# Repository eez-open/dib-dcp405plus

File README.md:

### This is a WORK IN PROGRESS!

---

### Ownership and License
The contributors are listed in CONTRIB.TXT. 

Licenses | OSHWA UID
--|--
 | 

### Overview

The EEZ DIB DCP405+ Power module is an improved version of the [DCP405](https://github.com/eez-open/modular-psu/tree/master/dcp405) module that now includes an on-board 32-bit MCU, a more accurate and faster A/D converter for simultaneous voltage and current measurement (and thus more accurate power measurement).
This version features remote current programming in addition to the existing remote voltage programming. Sense inputs are also on 4 mm safety sockets, which now enables usage of widely available (e.g. AliExpress, eBay, etc.) and affordable Kelvin cable sets (Power/Sense) usually used with LCR meters (see below)

### Feature list
- Power input: 48 Vdc (e.g. Mean Well EPP-150-48 or LRS-150F-48)
- Max. output power: 155 W (as limited with Mean Well AC/DC module capacity) 
- Voltage regulation (CV), 0 – 40 V. Voltage set resolution (_U_SET_): 16-bit, read resolution (_U_MON_): 15-bit
- Current regulation (CC) with 2-range (50 mA, 5 A). Current set resolution (_I_SET_): 16-bit, Current read resolution (_I_MON_): 20-bit for each range
- On-board low EMI switching power pre-regulator and bias power supply
- On-board OVP with full range dual crowbar (triac/MOSFET) and 20x5 mm fuse
- Down-programmer
- Output enable (OE) circuit with LED indicator combined with coupling indication
- Ø4 mm sockets (19.05 mm/0.75” pitch) for Power outputs and Sense inputs 
- Pass-thru connector for power output coupling with other power boards for e.g. doubling output voltage (up to 80 V) or current (up to 10 A)
- Remote voltage sense with LED indicator and inverse polarity protection
- Remote voltage and current programming with LED indicator (+2.5 V for full range)
- On-board 32-bit 250 MHz MCU ([STM32H503CBT6](https://www.st.com/en/microcontrollers-microprocessors/stm32h503cb.html))
- Galvanically isolated SPI bus
- I2C EEPROM for storing board specific configuration and calibration parameters
- SPI Temperature sensor
- Dimensions: 180 x 103.5 mm, 4-layer PCB
- **CE certified design**

---

This work is financed by [NLnet](https://nlnet.nl/project/BB3-CM5/) foundation

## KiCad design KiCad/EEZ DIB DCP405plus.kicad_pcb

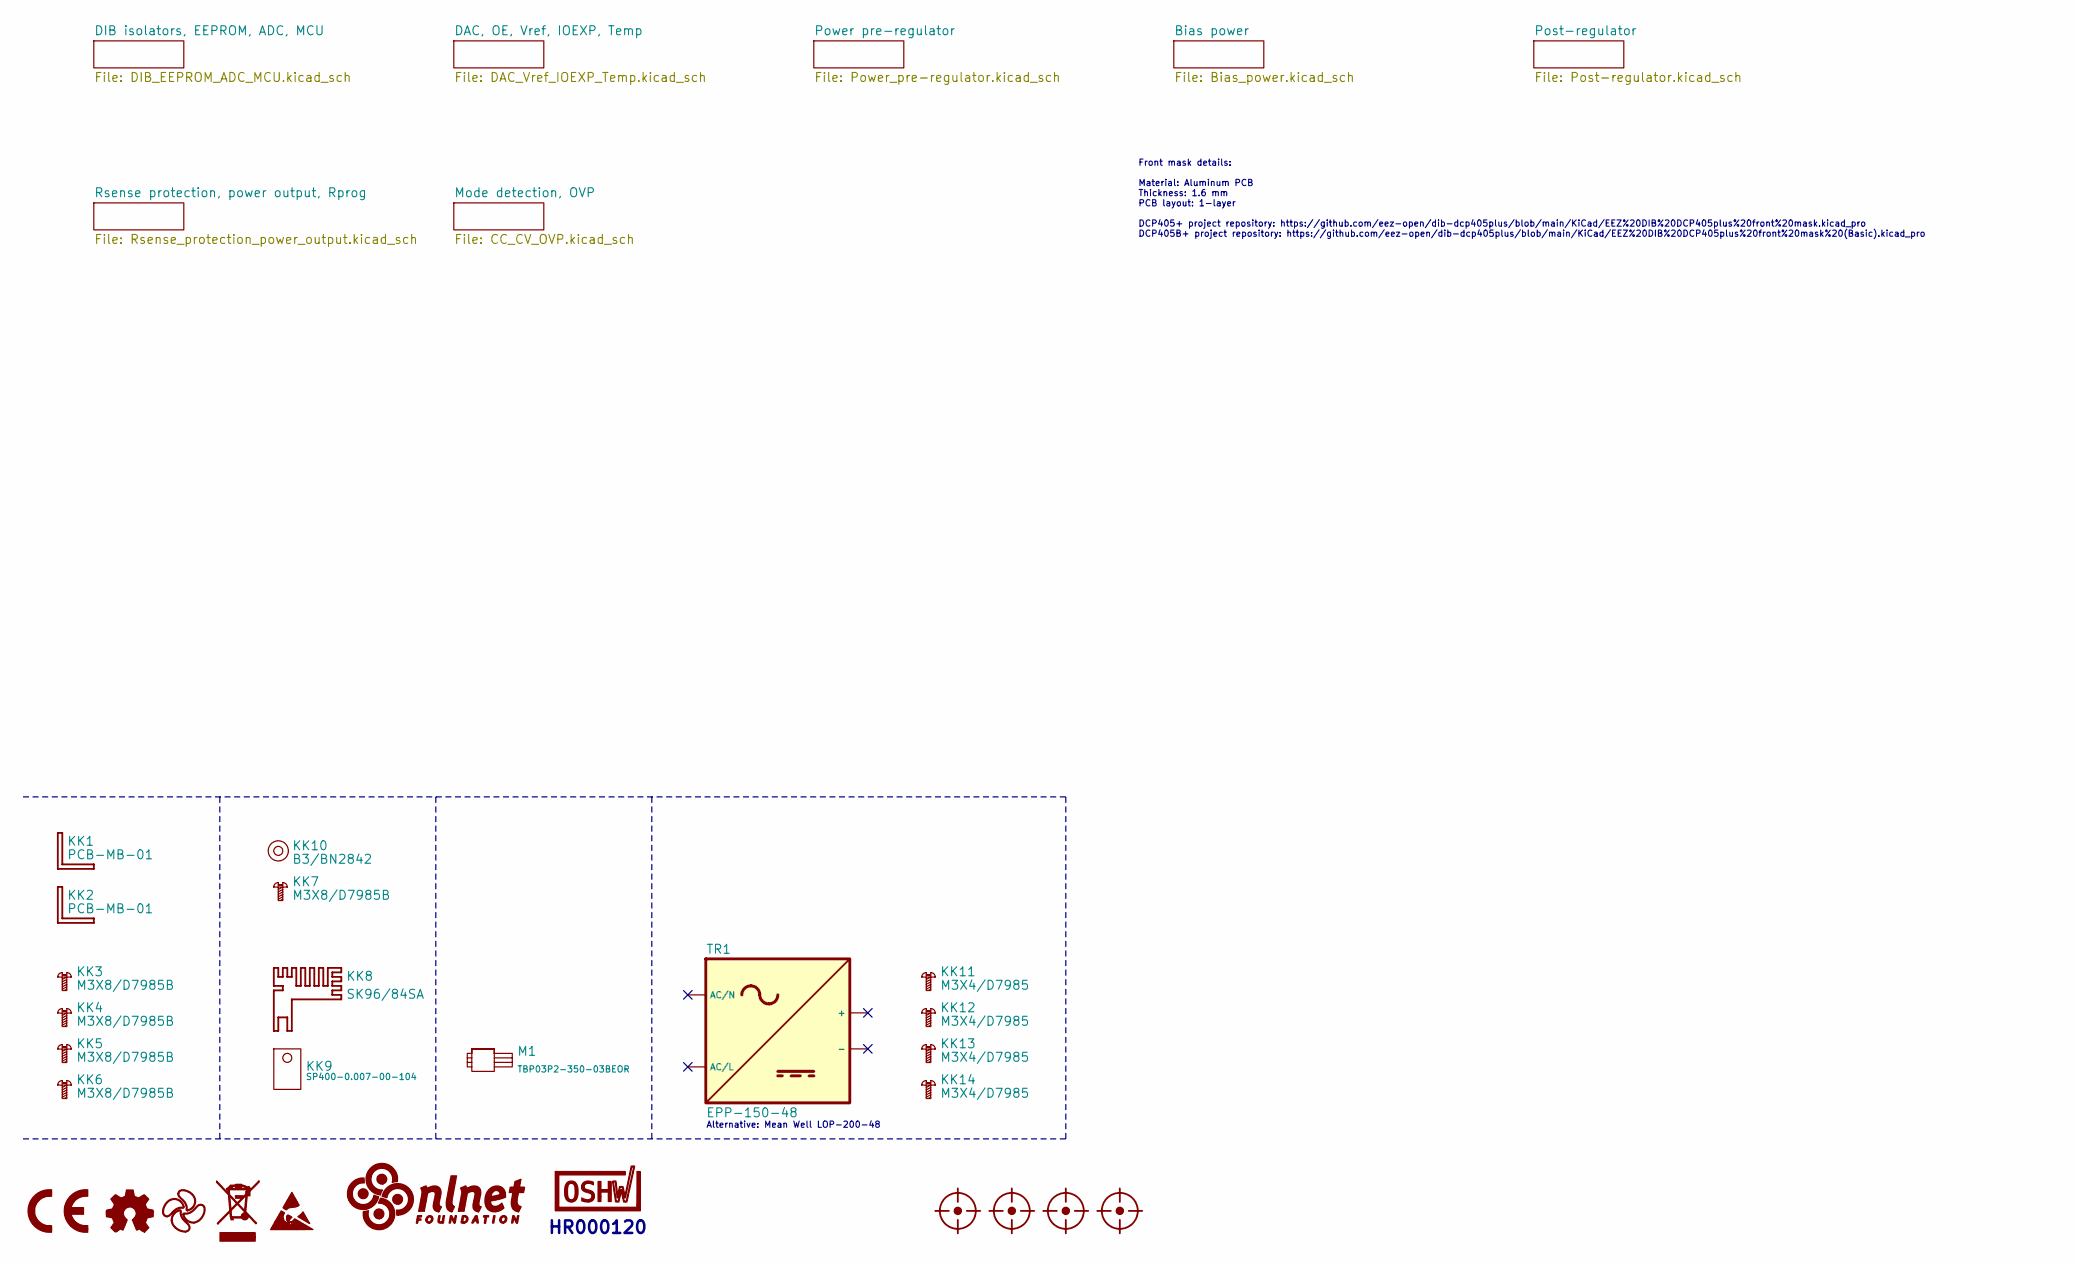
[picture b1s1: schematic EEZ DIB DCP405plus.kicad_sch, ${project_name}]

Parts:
FM1, FM2, FM3, FM4: FIDUCIAL; Fiducial_0.75mm_Mask1.5mm
KK1, KK2: PCB-MB-01; DigiKey RPC1760-ND
KK3, KK4, KK5, KK6, KK7: M3X8/D7985B
KK8: SK96/84SA; SK96_84; DigiKey 5496-SK9684SA-ND
KK9: SP400-0.007-00-104; DigiKey BER204-ND
KK10: B3/BN2842
KK11, KK12, KK13, KK14: M3X4/D7985
LOGO1: CR logo; CE logo
LOGO2: Open HW logo
LOGO3: EEZ logo; EEZ logo (outline 6mm)
LOGO4: WEEE logo
LOGO5: ESD logo
LOGO6: NLnet logo
LOGO7: OSHWA logo; OSHWA logo 6.6mm
M1: TBP03P2-350-03BEOR; DigiKey 2223-TBP03P2-350-03BEOR-ND
TR1: EPP-150-48; DigiKey 1866-LOP-200-48-ND

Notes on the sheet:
Alternative: Mean Well LOP-200-48
HR000120
Front mask details: Material: Aluminum PCB Thickness: 1.6 mm PCB layout: 1-layer DCP405+ project repository: https://github.com/eez-open/dib-dcp405plus/blob/main/KiCad/EEZ%20DIB%20DCP405plus%20front%20mask.kicad_pro DCP405B+ project repository: https://github.com/eez-open/dib-dcp405plus/blob/main/K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

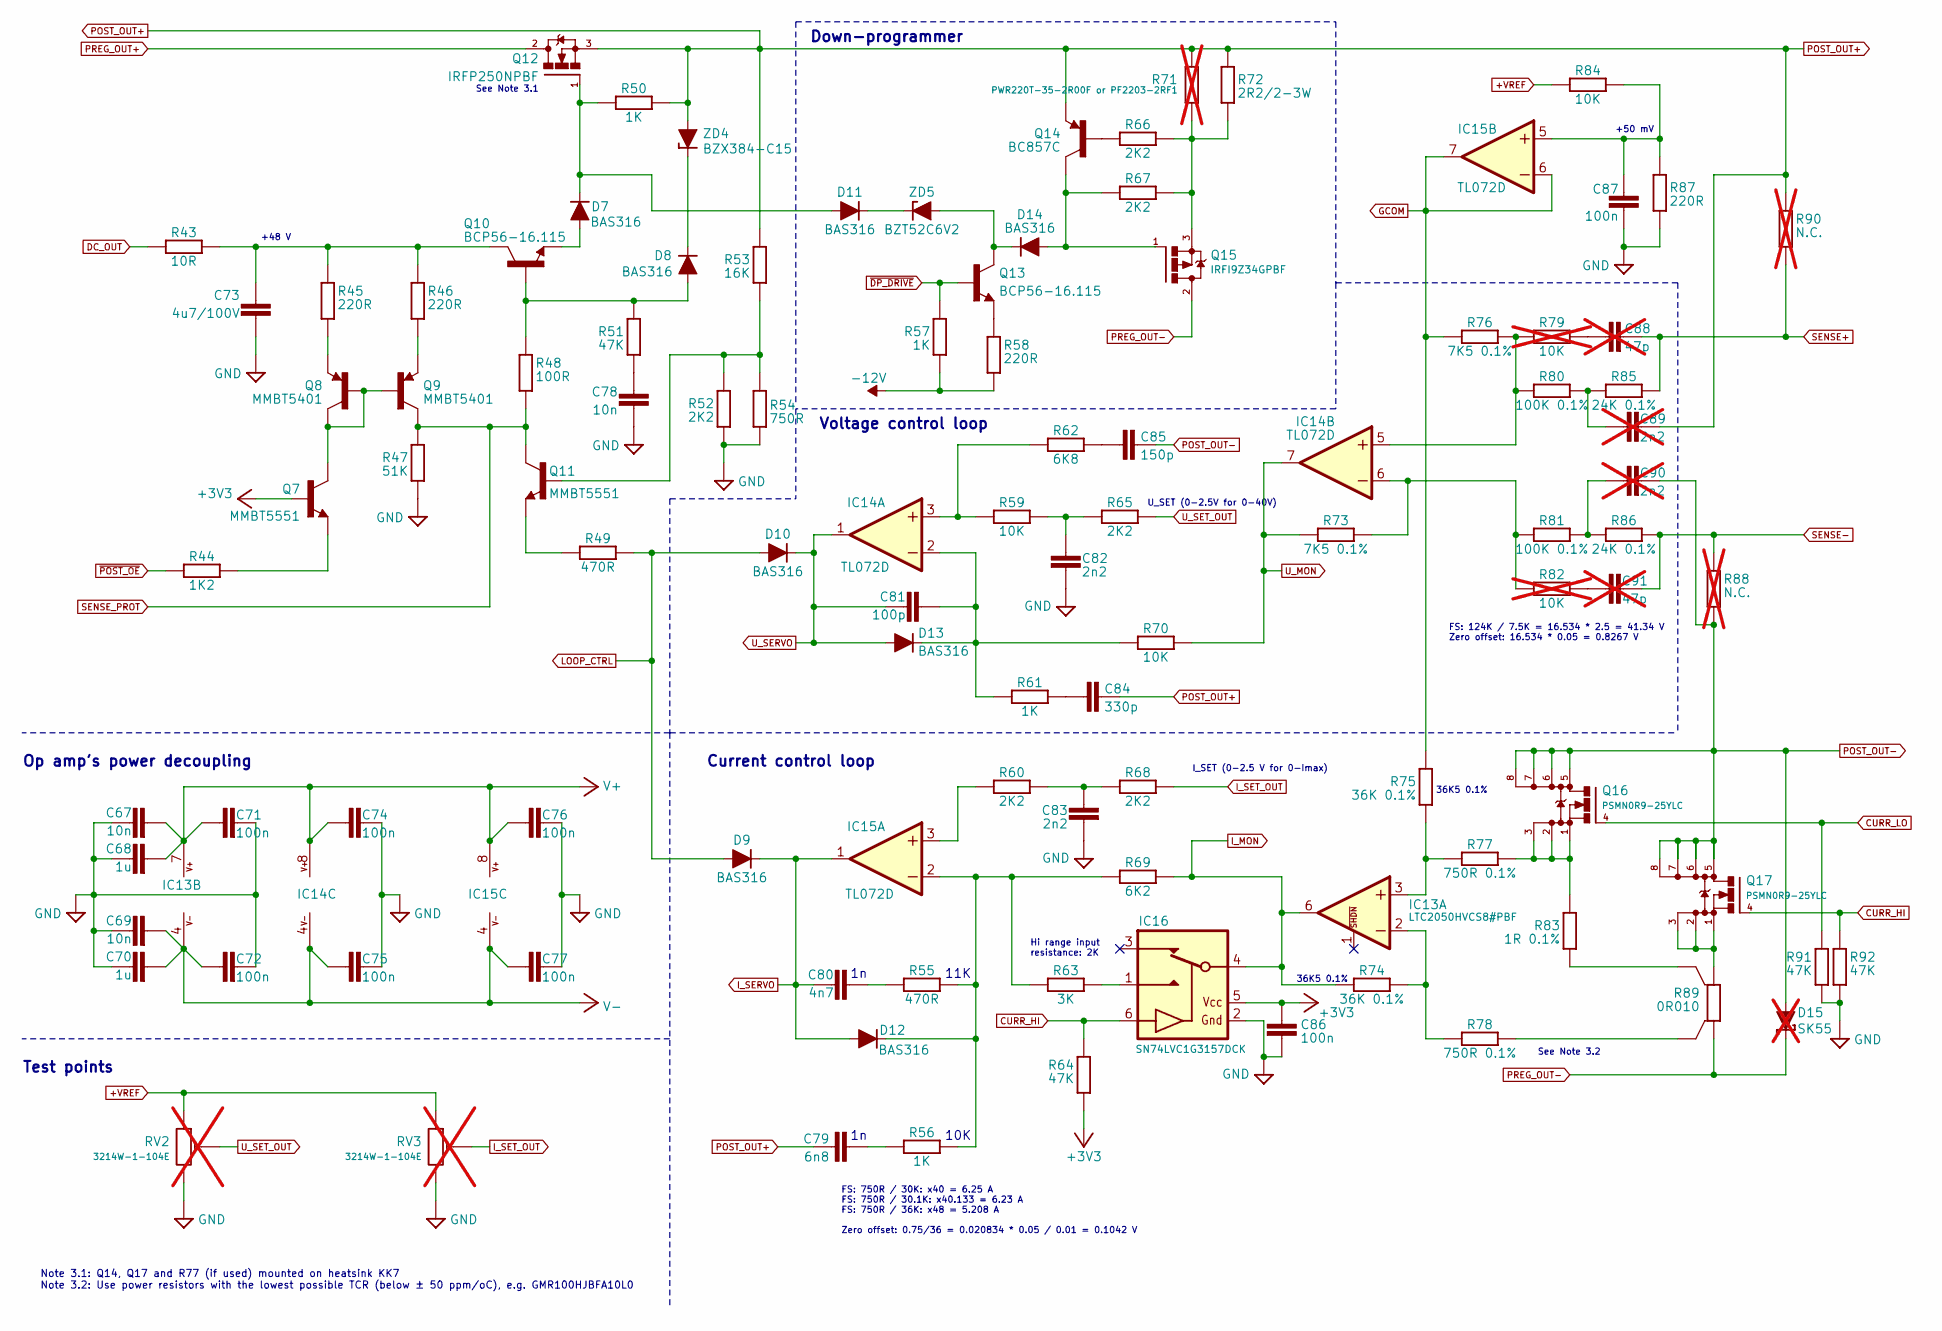
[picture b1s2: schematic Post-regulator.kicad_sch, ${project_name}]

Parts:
C67, C69, C78: 10n; C_0805_2012Metric; DigiKey 490-7194-1-ND
C68, C70: 1u; C_0805_2012Metric; DigiKey 1276-2931-1-ND
C71, C72, C74, C75, C76, C77, C86, C87: 100n; C_0603_1608Metric; DigiKey 1276-6717-1-ND
C73: 4u7/100V; C_1210_3225Metric; DigiKey 587-5034-1-ND
C79: 6n8; C_0805_2012Metric; DigiKey 399-C0805C682K5RACTUCT-ND
C80: 4n7; C_0805_2012Metric; DigiKey 732-12255-1-ND
C81: 100p; C_0805_2012Metric; DigiKey 399-15000-1-ND
C82, C83: 2n2; C_0805_2012Metric; DigiKey 1276-2478-1-ND
C84: 330p; C_0805_2012Metric; DigiKey 311-1117-1-ND
C85: 150p; C_0805_2012Metric; DigiKey 732-7853-1-ND
C88, C91: 47p; C_0805_2012Metric; not fitted
C89, C90: 2n2; C_0805_2012Metric; DigiKey 399-C0805C222K5RAC7210TR-ND; not fitted
D7, D8, D9, D10, D11, D12, D13, D14: BAS316; SOD-323_1P8X1P35_ONS-M; DigiKey 5399-BAS316CT-ND
D15: SK55; DO214AA; DigiKey SK56A-LTPMSCT-ND; not fitted
IC13: LTC2050HVCS8#PBF; SOIC127P600X173-8N; DigiKey LTC2050HVCS8#TRPBFCT-ND
IC14, IC15: TL072D; SOIC127P600X173-8N; DigiKey 296-1282-1-ND
IC16: SN74LVC1G3157DCK; SOT65P210X110-6N; DigiKey 296-14909-1-ND
Q7, Q11: MMBT5551; SOT23-BEC; DigiKey MMBT5551LT1GOSCT-ND
Q8, Q9: MMBT5401; SOT23-BEC; DigiKey MMBT5401-FDICT-ND
Q10, Q13: BCP56-16.115; SOT223-BCE; DigiKey 5399-BCP56-16CT-ND
Q12: IRFP250NPBF; TO247-3_SUNKEN; DigiKey IRFP250PBF-ND
Q14: BC857C; SOT23-BEC; DigiKey 4878-BC857CCT-ND
Q15: IRFI9Z34GPBF; TO220FP-V; DigiKey IRFI9Z34GPBF-ND
Q16, Q17: PSMN0R9-25YLC; TDSON-8; DigiKey 1727-5292-1-ND
R43: 10R; R_0805_2012Metric; DigiKey 311-10.0CRCT-ND
R44: 1K2; R_0805_2012Metric; DigiKey 311-1.20KCRCT-ND
R45, R46, R58, R87: 220R; R_0805_2012Metric; DigiKey RMCF0805FT220RCT-ND
R47: 51K; R_0805_2012Metric; DigiKey 311-51.0KCRCT-ND
R48: 100R; R_0603_1608Metric; DigiKey 13-RC0603FR-10100RLCT-ND
R49, R55: 470R; R_0805_2012Metric; DigiKey 13-RC0805FR-13470RLCT-ND
R50, R56, R57, R61: 1K; R_0805_2012Metric; DigiKey 311-1.00KCRCT-ND
R51, R64, R91, R92: 47K; R_0805_2012Metric; DigiKey RHM47KKCT-ND
R52, R60, R65, R66, R67, R68: 2K2; R_0805_2012Metric; DigiKey 311-2.20KCRCT-ND
R53: 16K; R_0805_2012Metric; DigiKey 311-16.0KCRCT-ND
R54: 750R; R_0805_2012Metric; DigiKey A126385CT-ND
R59, R70, R84: 10K; R_0805_2012Metric; DigiKey 311-10.0KCRCT-ND
R62: 6K8; R_0805_2012Metric; DigiKey 311-6.80KCRCT-ND
R63: 3K; R_0603_1608Metric; DigiKey 311-3.00KCRCT-ND
R69: 6K2; R_0805_2012Metric; DigiKey 311-6.20KCRCT-ND
R71: PWR220T-35-2R00F or PF2203-2RF1; TO220-2-V; DigiKey 696-1313-ND; not fitted
R72: 2R2/2-3W; R_2512_6332Metric; DigiKey CRM2512-JW-2R2ELFCT-ND
R73, R76: 7K5 0.1%; R_0805_2012Metric; DigiKey YAG1974CT-ND
R74, R75: 36K 0.1%; R_0805_2012Metric; DigiKey YAG4886CT-ND
R77, R78: 750R 0.1%; R_0805_2012Metric; DigiKey YAG4940CT-ND
R79, R82: 10K; R_0805_2012Metric; not fitted
R80, R81: 100K 0.1%; R_0805_2012Metric; DigiKey YAG4808CT-ND
R83: 1R 0.1%; R_1206_3216Metric; DigiKey 1712-CPF1206B1R0E1CT-ND
R85, R86: 24K 0.1%; R_0805_2012Metric; DigiKey P24KBFCT-ND
R88, R90: N.C.; R_0805_2012Metric; not fitted
R89: 0R010; R_2512-4WIRE; DigiKey 846-GMR100HJBFA10L0CT-ND
RV2, RV3: 3214W-1-104E; TRIM_3214W-1-104E; DigiKey 3214W-104ECT-ND; not fitted
ZD4: BZX384-C15; SOD-323_1P8X1P35_ONS-M; DigiKey 1727-BZX384-C15-QFCT-ND
ZD5: BZT52C6V2; SOD123; DigiKey 4878-BZT52C6V2CT-ND

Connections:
+3V3: C86.1, IC16.5 (VDD), Q7.B, R64.1; also elsewhere on the board
+VREF: R84.1, RV2.1, RV3.1; also elsewhere on the board
-12V: R57.2, R58.2; also elsewhere on the board
CURR_HI: IC16.6 (CTRL), Q17.4 (G), R64.2, R92.2; also elsewhere on the board
CURR_LO: Q16.4 (G), R91.2; also elsewhere on the board
DC_OUT: R43.2; also elsewhere on the board
GCOM: IC15.6 (-IN), IC15.7 (OUT), R75.1, R76.1; also elsewhere on the board
GND: C67.1, C68.1, C69.1, C70.1, C71.2, C72.2, C73.2, C74.1, C75.1, C76.1, C77.1, C78.2, C82.2, C83.2, C86.2, C87.2, IC16.2 (GND), R47.1, R52.1, R54.1, R87.2, R91.1, R92.1, RV2.3, RV3.3; also elsewhere on the board
I_MON: IC13.6 (OUT), IC16.4 (COM), R69.1, R74.2; also elsewhere on the board
I_SERVO: C80.2, D9.C, D12.A, IC15.1 (OUT); also elsewhere on the board
I_SET_OUT: R68.1, RV3.2; also elsewhere on the board
LOOP_CTRL: D9.A, D10.A, R49.1; also elsewhere on the board
unnamed: C73.1, Q10.C, R43.1, R45.2, R46.2
unnamed: C78.1, R51.1
unnamed: C79.2, R56.1
unnamed: C80.1, R55.1
unnamed: C82.1, R59.1, R65.2
unnamed: C83.1, R60.1, R68.2
unnamed: C84.2, R61.1
unnamed: C85.2, R62.1
unnamed: C88.2, R79.1
unnamed: C89.1, R80.2, R85.1
unnamed: C90.1, R81.2, R86.1
unnamed: C91.2, R82.1
unnamed: D7.A, Q10.E
unnamed: D8.A, Q10.B, R48.1, R51.2
unnamed: D8.C, ZD4.C
unnamed: D11.C, ZD5.C
unnamed: D14.C, Q13.C, ZD5.A
unnamed: IC13.3 (+IN), R75.2, R77.2
unnamed: IC13.2 (-IN), R74.1, R78.2
unnamed: IC14.3 (+IN), R59.2, R62.2
unnamed: C81.1, D13.C, IC14.2 (-IN), R61.2, R70.2
unnamed: IC14.5 (+IN), R76.2, R79.2, R80.1
unnamed: IC14.6 (-IN), R73.2, R81.1, R82.2
unnamed: IC15.3 (+IN), R60.2
unnamed: D12.C, IC15.2 (-IN), R55.2, R56.2, R63.2, R69.2
unnamed: C87.1, IC15.5 (+IN), R84.2, R87.1
unnamed: IC16.1 (NO), R63.1
unnamed: Q7.C, Q8.B, Q8.C, Q9.B
unnamed: Q7.E, R44.2
unnamed: Q8.E, R45.1
unnamed: Q9.E, R46.1
unnamed: Q11.B, R52.2, R53.1, R54.2
unnamed: Q11.E, R49.2
unnamed: D7.C, D11.A, Q12.1 (G), R50.1
unnamed: Q13.E, R58.1
unnamed: Q14.B, R66.2
unnamed: D14.A, Q14.C, Q15.1 (G), R67.2
unnamed: Q15.3 (S), R66.1, R67.1, R71.1, R72.2
unnamed: Q16.1 (S), Q16.2 (S), Q16.3 (S), R77.1, R83.2
unnamed: Q17.1 (S), Q17.2 (S), Q17.3 (S), R89.2
unnamed: R78.1, R89.1S
unnamed: R83.1, R89.2S
POST_OUT+: C79.1, C84.1, C89.2, Q12.3 (S), Q14.E, R50.2, R53.2, R71.2, R72.1, R90.1, ZD4.A; also elsewhere on the board
POST_OUT-: C85.1, C90.2, D15.A, Q16.5 (D), Q16.6 (S), Q16.7 (S), Q16.8 (S), Q17.5 (D), Q17.6 (S), Q17.7 (S), Q17.8 (S), R88.2; also elsewhere on the board
PREG_OUT+: Q12.2 (D); also elsewhere on the board
PREG_OUT-: D15.C, Q15.2 (D), R89.1; also elsewhere on the board
SENSE+: C88.1, R85.2, R90.2; also elsewhere on the board
SENSE-: C91.1, R86.2, R88.1; also elsewhere on the board
SENSE_PROT: Q9.C, Q11.C, R47.2, R48.2; also elsewhere on the board
U_MON: IC14.7 (OUT), R70.1, R73.1; also elsewhere on the board
U_SERVO: C81.2, D10.C, D13.A, IC14.1 (OUT); also elsewhere on the board
U_SET_OUT: R65.1, RV2.2; also elsewhere on the board
V+: C67.2, C68.2, C71.1, C74.2, C76.2, IC13.7 (V+), IC14.8 (V+), IC15.8 (V+); also elsewhere on the board
V-: C69.2, C70.2, C72.1, C75.2, C77.2, IC13.4 (V-), IC14.4 (V-), IC15.4 (V-); also elsewhere on the board
~DP_DRIVE: Q13.B, R57.1; also elsewhere on the board
~POST_OE: R44.1; also elsewhere on the board

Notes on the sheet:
Hi range input resistance: 2K
FS: 124K / 7.5K = 16.534 * 2.5 = 41.34 V Zero offset: 16.534 * 0.05 = 0.8267 V
11K
Down-programmer
+50 mV
I_SET (0-2.5 V for 0-Imax)
Op amp's power decoupling
See Note 3.1
36K5 0.1%
10K
Current control loop
Voltage control loop
See Note 3.2
+48 V
U_SET (0-2.5V for 0-40V)
Test points
FS: 750R / 30K: x40 = 6.25 A FS: 750R / 30.1K: x40.133 = 6.23 A FS: 750R / 36K: x48 = 5.208 A Zero offset: 0.75/36 = 0.020834 * 0.05 / 0.01 = 0.1042 V
Note 3.1: Q14, Q17 and R77 (if used) mounted on heatsink KK7 Note 3.2: Use power resistors with the lowest possible TCR (below ± 50 ppm/oC), e.g. GMR100HJBFA10L0

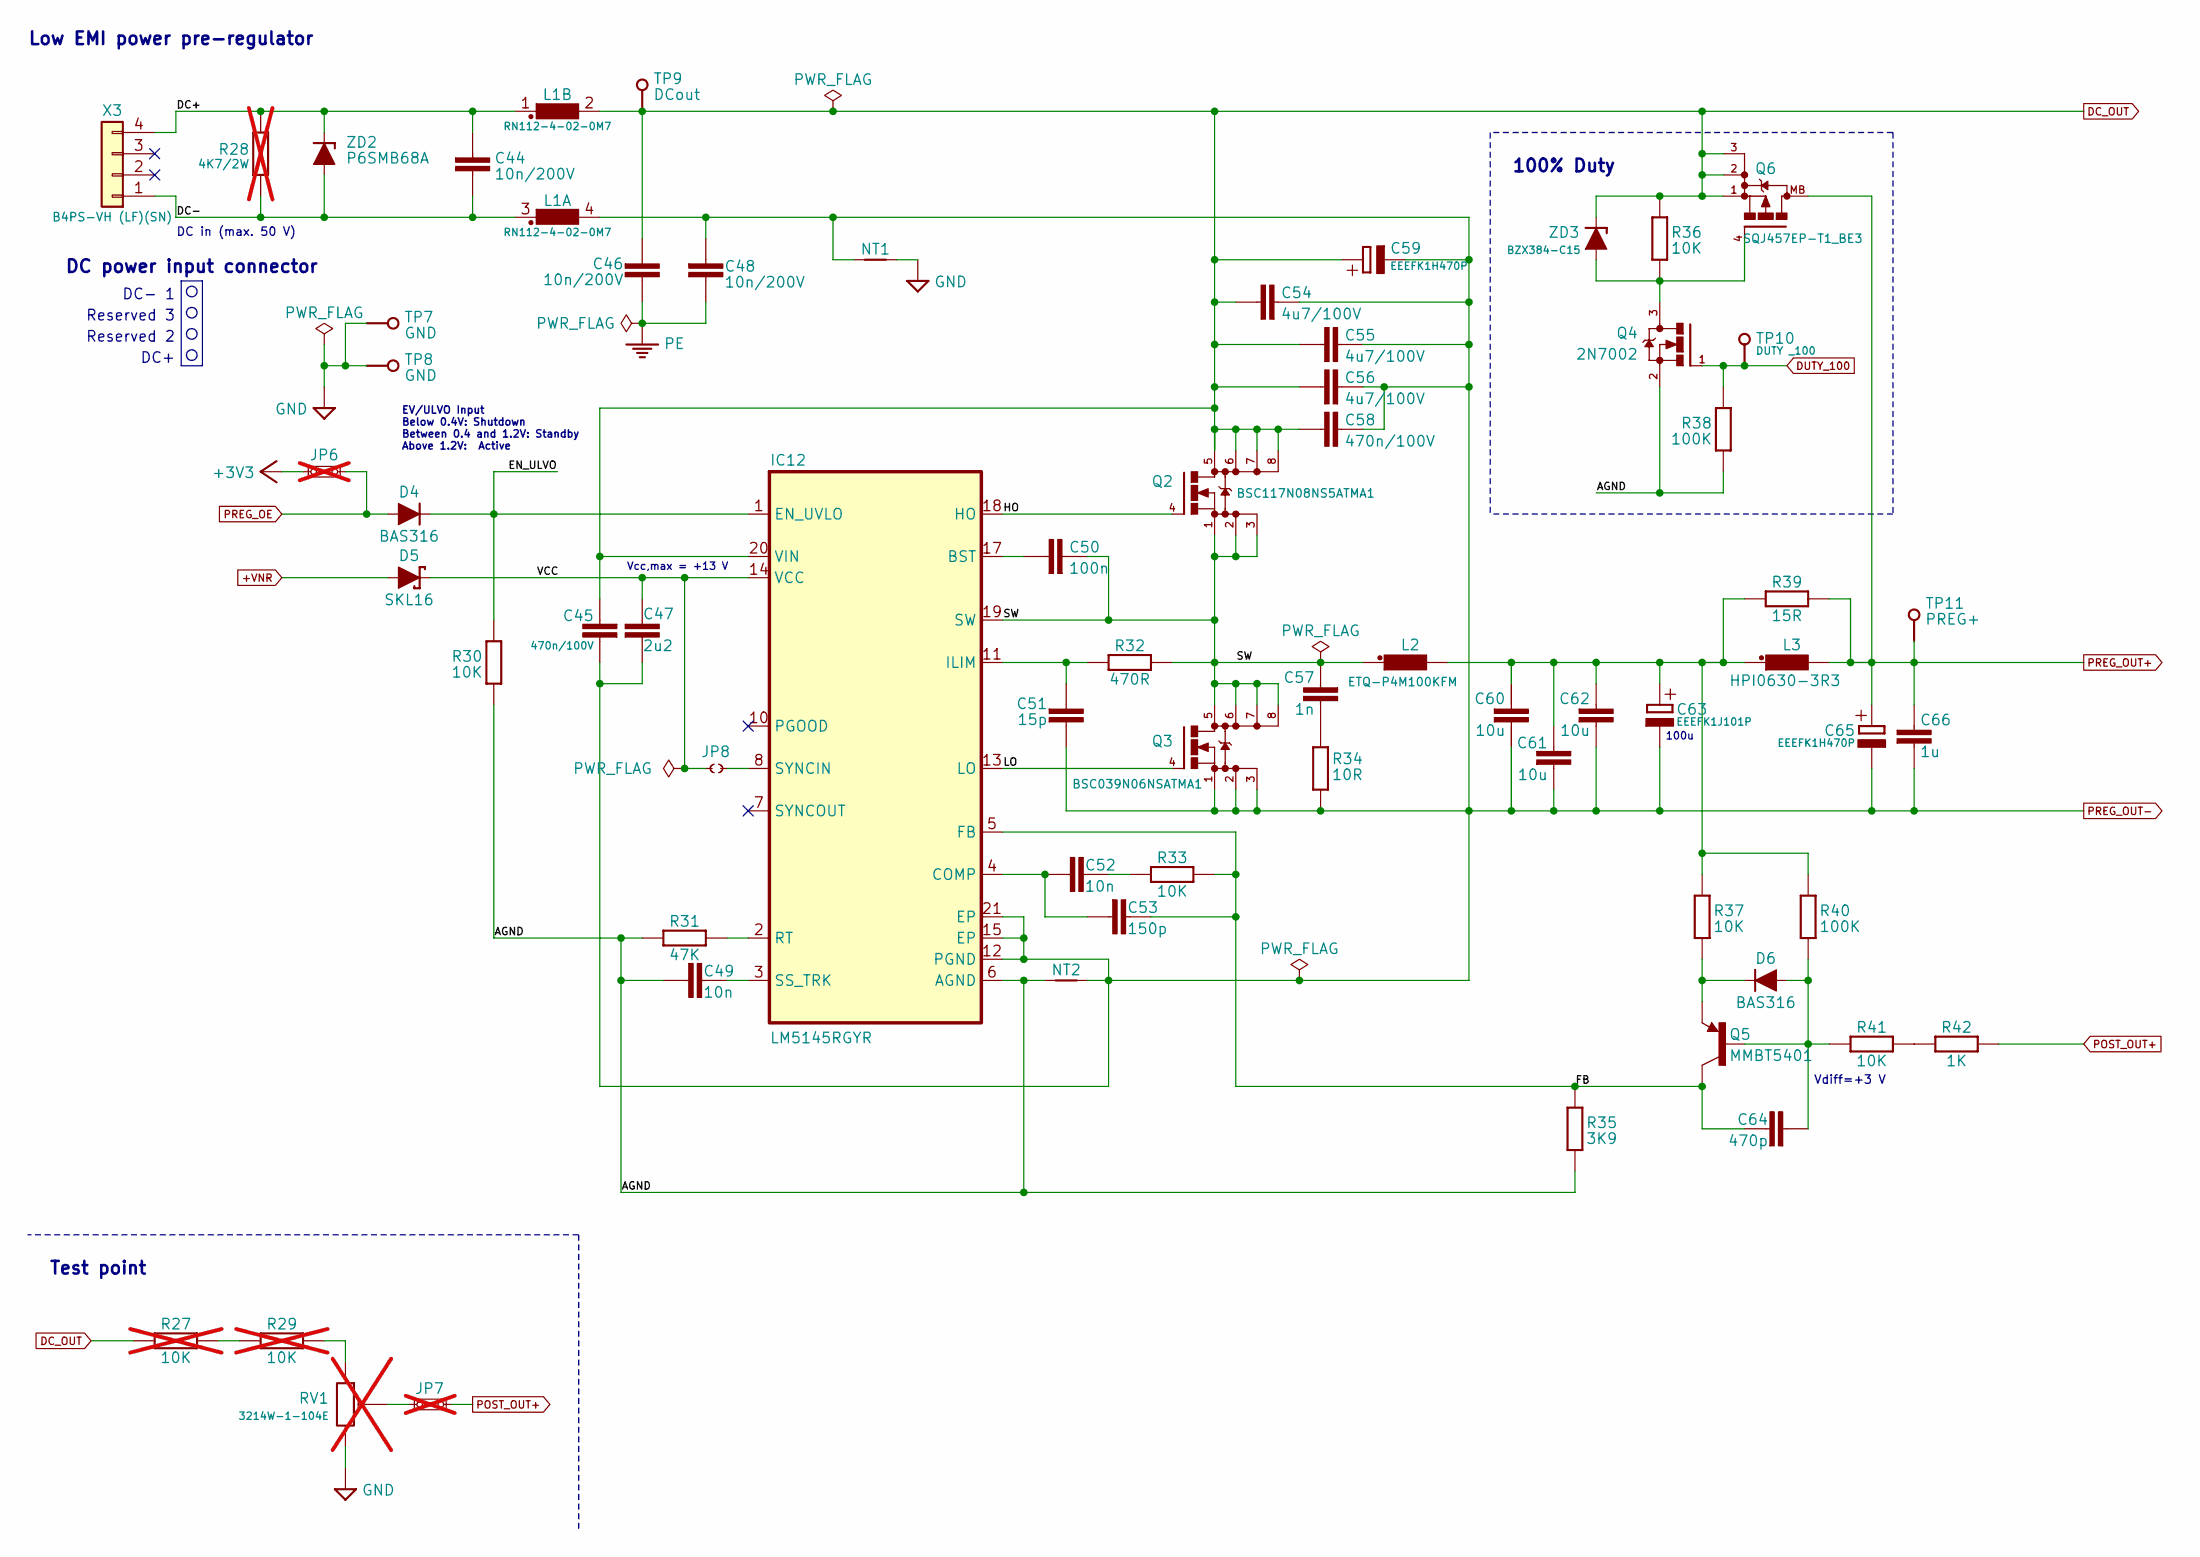
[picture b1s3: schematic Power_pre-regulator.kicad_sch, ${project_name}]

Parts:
C44, C46, C48: 10n/200V; C_1206_3216Metric; DigiKey 311-4491-1-ND
C45, C58: 470n/100V; C_0805_2012Metric; DigiKey 587-5014-1-ND
C47: 2u2; C_1206_3216Metric; DigiKey 1276-3138-1-ND
C49, C52: 10n; C_0805_2012Metric; DigiKey 490-7194-1-ND
C50: 100n; C_0603_1608Metric; DigiKey 1276-6717-1-ND
C51: 15p; C_0603_1608Metric; DigiKey 732-7847-1-ND
C53: 150p; C_0805_2012Metric; DigiKey 732-7853-1-ND
C54, C55, C56: 4u7/100V; C_1210_3225Metric; DigiKey 587-5034-1-ND
C57: 1n; C_0603_1608Metric; DigiKey 1276-1018-1-ND
C59, C65: EEEFK1H470P; CAPAE830X1050N; DigiKey PCE3815CT-ND
C60, C61, C62: 10u; C_1210_3225Metric; DigiKey 1276-3387-1-ND
C63: EEEFK1J101P; CAPAE1030X1050N; DigiKey PCE3819CT-ND
C64: 470p; C_0805_2012Metric; DigiKey 732-7837-1-ND
C66: 1u; C_0805_2012Metric; DigiKey 1276-2931-1-ND
D4, D6: BAS316; SOD-323_1P8X1P35_ONS-M; DigiKey 5399-BAS316CT-ND
D5: SKL16; SOD123; DigiKey RB160MM-60CT-ND
IC12: LM5145RGYR; RGY0020B; DigiKey 296-47121-1-ND
JP6, JP7: M22-2010246; DigiKey M22-2010346-ND; not fitted
JP8: JP2-CUT-0805; JP2 open (0603)
L1: RN112-4-02-0M7; RN112; DigiKey 817-2100-ND
L2: ETQ-P4M100KFM; PANASONIC_ETQ-P4_KFM; DigiKey P124167CT-ND
L3: HPI0630-3R3; COILCRAFT_HPI0630; DigiKey 445-180834-1-ND
NT1: NetTie_2; NetTie-2_SMD_Pad1.5mm
NT2: NetTie_2; NetTie-2_SMD_Pad0.2mm
Q2: BSC117N08NS5ATMA1; TDSON-8; DigiKey BSC117N08NS5ATMA1CT-ND
Q3: BSC039N06NSATMA1; TDSON-8; DigiKey BSC039N06NSATMA1CT-ND
Q4: 2N7002; SOT103P240X110-3N; DigiKey T2N7002AKLMCT-ND
Q5: MMBT5401; SOT23-BEC; DigiKey MMBT5401-FDICT-ND
Q6: SQJ457EP-T1_BE3; PowerPAK SO-8; DigiKey 742-SQJ457EP-T1_BE3CT-ND
R27, R29: 10K; R_0805_2012Metric; DigiKey 311-10.0KCRCT-ND; not fitted
R28: 4K7/2W; R_2512_6332Metric; not fitted
R30, R33, R36, R37, R41: 10K; R_0805_2012Metric; DigiKey 311-10.0KCRCT-ND
R31: 47K; R_0805_2012Metric; DigiKey RHM47KKCT-ND
R32: 470R; R_0805_2012Metric; DigiKey 13-RC0805FR-13470RLCT-ND
R34: 10R; R_0805_2012Metric; DigiKey 311-10.0CRCT-ND
R35: 3K9; R_0805_2012Metric; DigiKey A126369CT-ND
R38, R40: 100K; R_0805_2012Metric; DigiKey RMCF0805FT100KCT-ND
R39: 15R; R_2010_5025Metric; DigiKey A129910CT-ND
R42: 1K; R_0805_2012Metric; DigiKey 311-1.00KCRCT-ND
RV1: 3214W-1-104E; TRIM_3214W-1-104E; DigiKey 3214W-104ECT-ND; not fitted
TP7, TP8: PCB_TEST_TABSHIELD; Testhole 24_50mils
TP9, TP10, TP11: TEST-PIN_0.9MM; Testhole 24_50mils
X3: B4PS-VH (LF)(SN); B4PS-VH; DigiKey 455-B4PS-VH-ND
ZD2: P6SMB68A; DO214AA; DigiKey P6SMB68ABBCT-ND
ZD3: BZX384-C15; SOD-323_1P8X1P35_ONS-M; DigiKey 1727-4986-1-ND

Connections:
+3V3: JP6.1; also elsewhere on the board
+VNR: D5.A; also elsewhere on the board
/Power pre-regulator/AGND: C49.2, IC12.6 (AGND), NT2.1, Q4.2 (S), R30.1, R31.1, R35.2, R38.2
/Power pre-regulator/DC+: C44.2, L1.1, R28.1, X3.4, ZD2.C
/Power pre-regulator/DC-: C44.1, L1.3 (1), R28.2, X3.1, ZD2.A
/Power pre-regulator/EN_ULVO: D4.C, IC12.1 (EN_UVLO), R30.2
/Power pre-regulator/FB: C53.1, C64.1, IC12.5 (FB), Q5.C, R33.2, R35.1
/Power pre-regulator/HO: IC12.18 (HO), Q2.4 (G)
/Power pre-regulator/LO: IC12.13 (LO), Q3.4 (G)
/Power pre-regulator/SW: C50.2, C57.1, IC12.19 (SW), L2.1, Q2.1 (S), Q2.2 (S), Q2.3 (S), Q3.5 (D), Q3.6 (S), Q3.7 (S), Q3.8 (S), R32.2
/Power pre-regulator/VCC: C47.2, D5.C, IC12.14 (VCC), JP8.1
DC_OUT: C45.2, C46.2, C54.1, C55.1, C56.1, C58.2, C59.+, IC12.20 (VIN), L1.2, Q2.5 (D), Q2.6 (S), Q2.7 (S), Q2.8 (S), Q6.1 (S), Q6.2 (S), Q6.3 (S), R27.2, R36.2, TP9.1 (P$1_1), ZD3.C; also elsewhere on the board
DUTY_100: Q4.1 (G), R38.1, TP10.1 (P$1_1); also elsewhere on the board
GND: NT1.2, RV1.3, TP7.1 (P$1_1), TP8.1 (P$1_1); also elsewhere on the board
unnamed: C52.1, R33.1
unnamed: C57.2, R34.2
unnamed: C60.1, C61.1, C62.1, C63.+, L2.2, L3.1, R37.1, R39.2, R40.1
unnamed: C64.2, D6.A, Q5.B, R40.2, R41.1
unnamed: D6.C, Q5.E, R37.2
unnamed: C50.1, IC12.17 (BST)
unnamed: C52.2, C53.2, IC12.4 (COMP)
unnamed: C51.1, IC12.11 (ILIM), R32.1
unnamed: IC12.2 (RT), R31.2
unnamed: C49.1, IC12.3 (SS_TRK)
unnamed: IC12.8 (SYNCIN), JP8.2
unnamed: JP7.1, RV1.2
unnamed: Q4.3 (D), Q6.4 (G), R36.1, ZD3.A
unnamed: R27.1, R29.2
unnamed: R29.1, RV1.1
unnamed: R41.2, R42.1
PE: C46.1, C48.2; also elsewhere on the board
POST_OUT+: JP7.2, R42.2; also elsewhere on the board
PREG_OE: D4.A, JP6.2; also elsewhere on the board
PREG_OUT+: C65.+, C66.2, L3.2, Q6.MB, R39.1, TP11.1 (P$1_1); also elsewhere on the board
PREG_OUT-: C45.1, C47.1, C48.1, C51.2, C54.2, C55.2, C56.2, C58.1, C59.-, C60.2, C61.2, C62.2, C63.-, C65.-, C66.1, IC12.12 (PGND), IC12.15 (EP), IC12.21 (EP), L1.4 (2), NT1.1, NT2.2, Q3.1 (S), Q3.2 (S), Q3.3 (S), R34.1; also elsewhere on the board

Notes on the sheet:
DC- 1
Reserved 2
Low EMI power pre-regulator
DC+
Vcc,max = +13 V
Reserved 3
DC in (max. 50 V)
100% Duty
Vdiff=+3 V
Test point
DC power input connector
100u
EV/ULVO Input Below 0.4V: Shutdown Between 0.4 and 1.2V: Standby Above 1.2V: Active

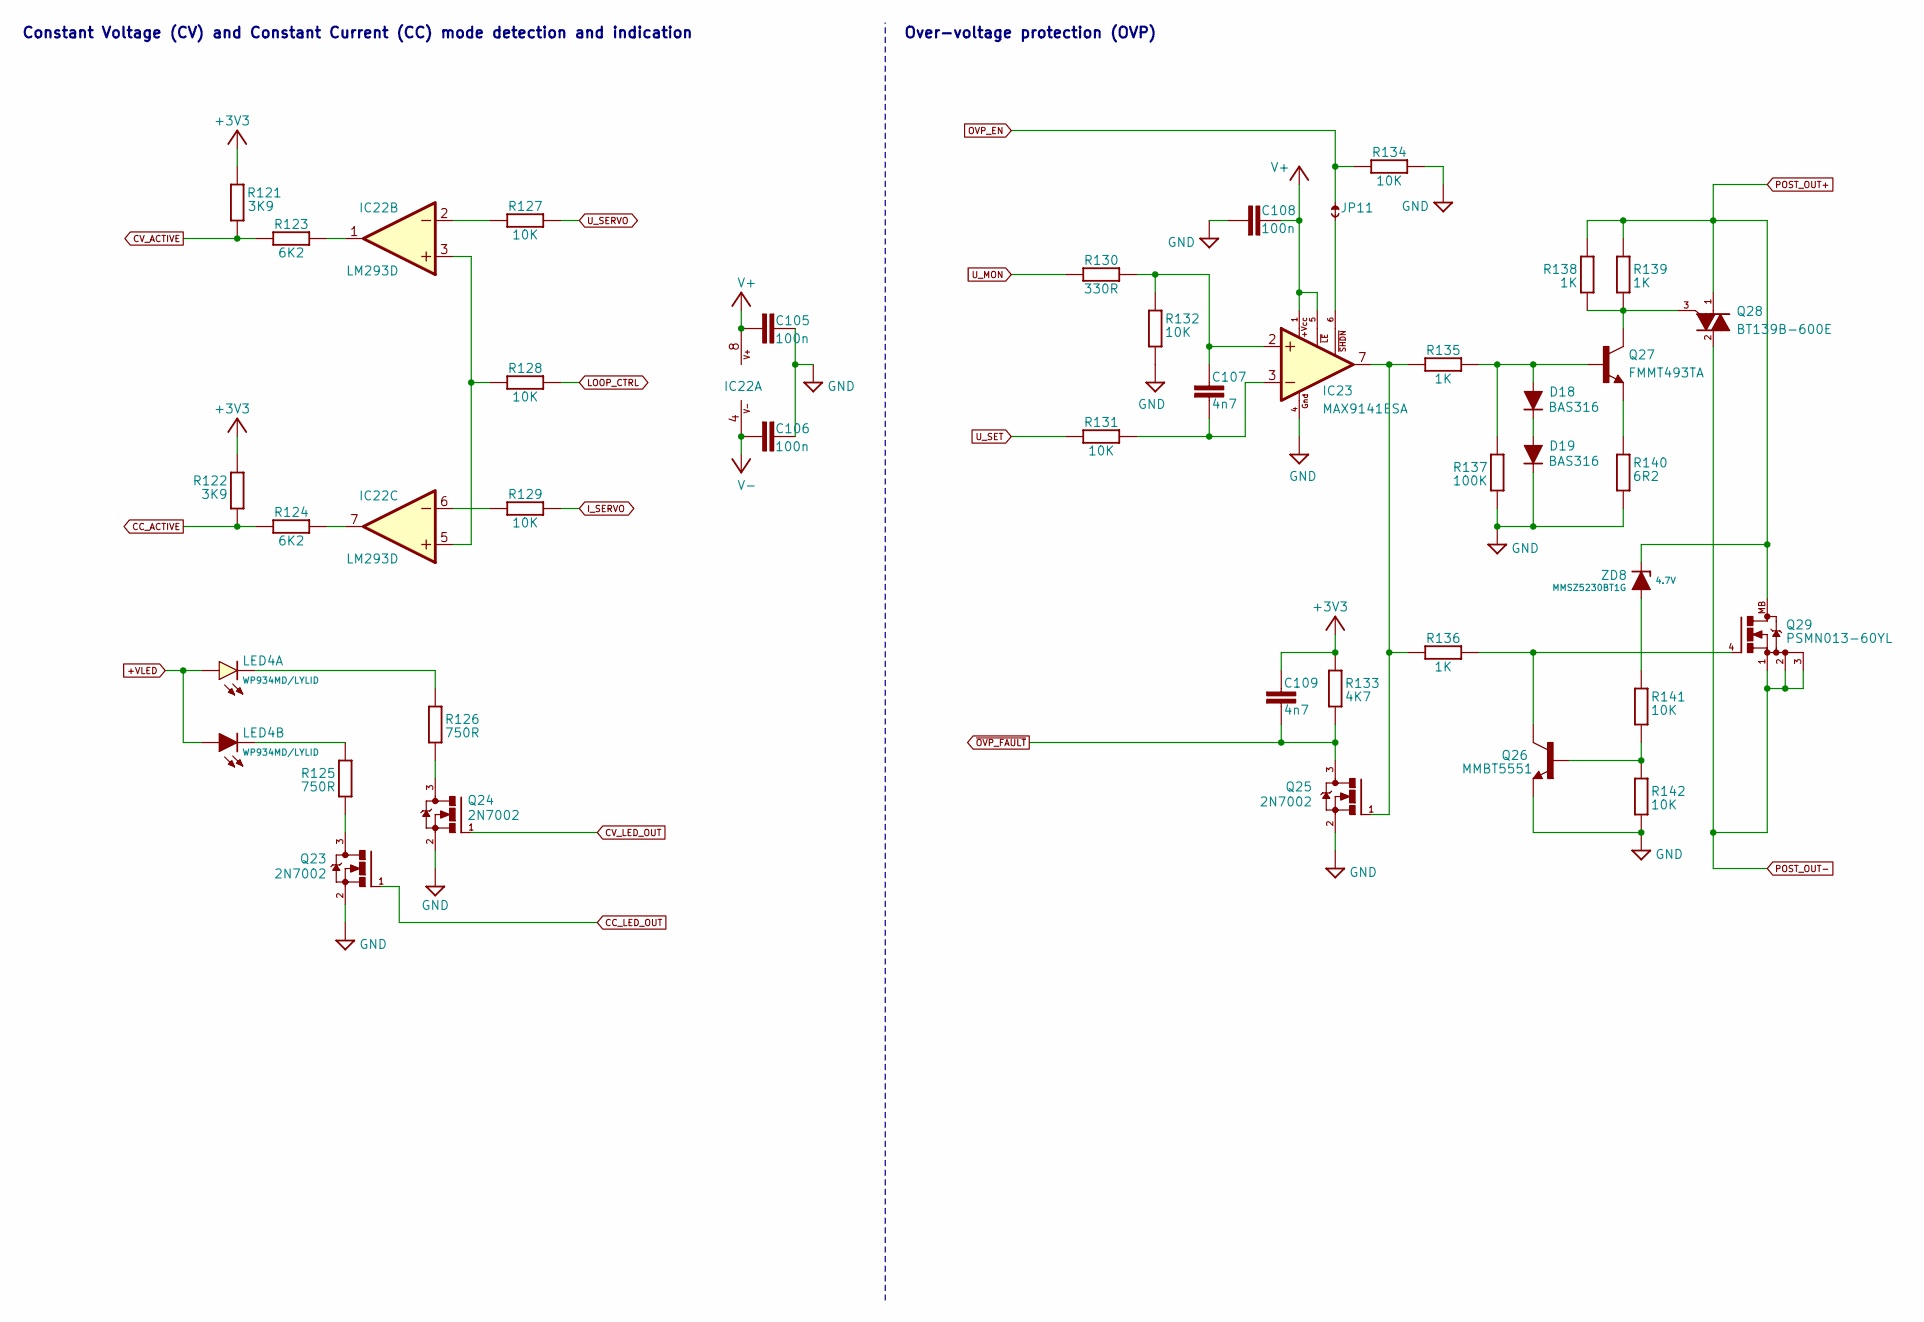
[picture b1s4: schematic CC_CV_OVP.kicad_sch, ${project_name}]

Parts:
C105, C106, C108: 100n; C_0603_1608Metric; DigiKey 1276-6717-1-ND
C107, C109: 4n7; C_0805_2012Metric; DigiKey 732-12255-1-ND
D18, D19: BAS316; SOD-323_1P8X1P35_ONS-M; DigiKey 5399-BAS316CT-ND
IC22: LM293D; SOIC127P600X173-8N; DigiKey LM293DR2GOSCT-ND
IC23: MAX9141ESA; SOIC127P600X173-8N; DigiKey MAX9141ESA+-ND
JP11: JP2-NOCUT-0805; JP2 shorted (0603)
LED4: WP934MD/LYLID; WP934MD_2YD; DigiKey 350-2716-ND
Q23, Q24, Q25: 2N7002; SOT103P240X110-3N; DigiKey T2N7002AKLMCT-ND
Q26: MMBT5551; SOT23-BEC; DigiKey MMBT5551LT1GOSCT-ND
Q27: FMMT493TA; SOT23-BEC; DigiKey FMMT493CT-ND
Q28: BT139B-600E; TO-263_SOT-404; DigiKey 1740-1290-1-ND
Q29: PSMN013-60YL; SOT669; DigiKey 1727-2589-1-ND
R121, R122: 3K9; R_0805_2012Metric; DigiKey A126369CT-ND
R123, R124: 6K2; R_0805_2012Metric; DigiKey 311-6.20KCRCT-ND
R125, R126: 750R; R_0805_2012Metric; DigiKey A126385CT-ND
R127, R128, R129, R131, R132, R134, R141, R142: 10K; R_0805_2012Metric; DigiKey 311-10.0KCRCT-ND
R130: 330R; R_0805_2012Metric; DigiKey A129743CT-ND
R133: 4K7; R_0805_2012Metric; DigiKey 311-4.70KCRCT-ND
R135, R136, R138, R139: 1K; R_0805_2012Metric; DigiKey 311-1.00KCRCT-ND
R137: 100K; R_0805_2012Metric; DigiKey RMCF0805FT100KCT-ND
R140: 6R2; R_0805_2012Metric; DigiKey 311-6.20CRCT-ND
ZD8: MMSZ5230BT1G; SOD123; DigiKey MMSZ4V7T1GOSCT-ND

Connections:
+3V3: C109.1, R121.2, R122.2, R133.1; also elsewhere on the board
+VLED: LED4.BA (A), LED4.TA (A); also elsewhere on the board
CC_ACTIVE: R122.1, R124.2; also elsewhere on the board
CC_LED_OUT: Q23.1 (G); also elsewhere on the board
CV_ACTIVE: R121.1, R123.2; also elsewhere on the board
CV_LED_OUT: Q24.1 (G); also elsewhere on the board
GND: C105.1, C106.1, C108.1, D19.C, IC23.4 (GND), Q23.2 (S), Q24.2 (S), Q25.2 (S), Q26.E, R132.2, R134.1, R137.1, R140.1, R142.1; also elsewhere on the board
I_SERVO: R129.1; also elsewhere on the board
LOOP_CTRL: R128.2; also elsewhere on the board
unnamed: D18.A, Q27.B, R135.1, R137.2
unnamed: D18.C, D19.A
unnamed: IC22.3 (+IN), IC22.5 (+IN), R128.1
unnamed: IC22.2 (-IN), R127.2
unnamed: IC22.1 (OUT), R123.1
unnamed: IC22.6 (-IN), R129.2
unnamed: IC22.7 (OUT), R124.1
unnamed: C107.1, IC23.2 (+IN), R130.2, R132.1
unnamed: C107.2, IC23.3 (-IN), R131.2
unnamed: IC23.7 (OUT), Q25.1 (G), R135.2, R136.2
unnamed: IC23.6 (~SHDN), JP11.2
unnamed: LED4.TC (C), R126.1
unnamed: LED4.BC (C), R125.2
unnamed: Q23.3 (D), R125.1
unnamed: Q24.3 (D), R126.2
unnamed: Q26.B, R141.1, R142.2
unnamed: Q27.E, R140.2
unnamed: Q27.C, Q28.3 (G), R138.1, R139.1
unnamed: Q26.C, Q29.4 (G), R136.1
unnamed: R141.2, ZD8.A
OVP_EN: JP11.1, R134.2; also elsewhere on the board
POST_OUT+: Q28.1 (A1), Q29.MB, R138.2, R139.2, ZD8.C; also elsewhere on the board
POST_OUT-: Q28.2 (A2), Q29.1 (S), Q29.2 (S), Q29.3 (S); also elsewhere on the board
U_MON: R130.1; also elsewhere on the board
U_SERVO: R127.1; also elsewhere on the board
U_SET: R131.1; also elsewhere on the board
V+: C105.2, C108.2, IC22.8 (V+), IC23.1 (+VCC), IC23.5 (~LE); also elsewhere on the board
V-: C106.2, IC22.4 (V-); also elsewhere on the board
~OVP_FAULT: C109.2, Q25.3 (D), R133.2; also elsewhere on the board

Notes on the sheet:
Constant Voltage (CV) and Constant Current (CC) mode detection and indication
Over-voltage protection (OVP)

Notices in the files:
parts and their libraries:
project_license: Licensed under the TAPR Open Hardware License (www.tapr.org/OHL)
